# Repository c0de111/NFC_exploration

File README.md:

# NFC exploration

Sandbox repo to explore **ST25DV04KC (ISO15693 / NFC-V)** tap-to-trigger flows for power control and waking circuits such as inki.

## Goal
Build a small, reproducible test platform (ST25DV04KC + **Raspberry Pi Pico/RP2040** + antenna + simple enclosure) to validate:
- RF-field / `V_EH` wake behavior in the real case
- Phone → tag writes (EEPROM / Type 5)
- MCU reads request over I²C and clears/acks
- End-to-end timing assumptions for a future “tap-to-book” workflow

## Current validated behavior
- ST25DV04KC bring-up over I2C is stable on Pico (`GP20/GP21`), with ST25 power switched by `GP18`.
- End-to-end NFC-V write from phone to tag user memory is working.
- Firmware parses 16-byte `INKI` request payloads from the last user-memory slot (`0x01F0` on ST25DV04KC).
- Firmware command opcode handling is active:
  - `0x11` -> `LED1` slow blink
  - `0x12` -> `LED1` fast blink (same onboard LED)
  - `0x01` -> legacy alias mapped to `LED1` slow blink
- Incomplete/invalid `INKI` frames are ignored (to avoid partial-write races).
- Valid requests are cleared only after `RF field` goes `OFF` (reduces interference with phone-side readback).
- Power latch is asserted early by Pico on boot (`GP28`) and auto-released after `NFC_AUTO_POWER_OFF_MS` (default `10000` ms).
- Runtime logging is event-driven: startup diagnostics once, then RF field edges and request actions only.

## Tuning firmware (antenna / power characterization)
A dedicated firmware (`nfc_tune`, source: `firmware/src/tune_main.c`) for real-time RF energy-harvesting characterization. It samples the ST25DV `V_EH` output via Pico ADC and renders a live scrolling bar graph in the terminal showing harvested power delta above baseline.

### What it measures
- ADC voltage on `V_EH` pin (default ADC1 = `GP27`), averaged and EMA-smoothed
- Delta above a startup baseline capture (no-RF reference)
- RF field state derived from voltage thresholds (configurable ON/OFF hysteresis)
- ST25 EH control register state (`EH_EN`, `EH_ON`, `FIELD_ON`, `VCC_ON`) via I2C

### Build and flash
```bash
make firmware-tune                    # build nfc_tune
# then either:
make firmware-tune-flash              # flash via SWD
# or drag-and-drop firmware/build/nfc_tune.uf2 in BOOTSEL mode
```

### Tuning workflow
1. Connect Pico via USB (serial + power).
2. Open terminal: `sudo tio /dev/ttyACM0`
3. Wait for baseline capture (keep RF away for ~2 seconds at boot).
4. Tap phone to antenna — the live graph shows `V_EH` delta in mV, RF ON/OFF transitions, session peak, and EH register state.
5. Adjust antenna matching (C2/C3 on `NFC_harness_V0`) and re-tap to compare coupling.
6. `Ctrl+C` to stop.

### Key CMake tuning parameters
All defaults are in `firmware/CMakeLists.txt`:
- `NFC_TUNE_ADC_INPUT` – ADC channel (default `1` = `GP27`)
- `NFC_TUNE_FIELD_ON_MV` / `NFC_TUNE_FIELD_OFF_MV` – RF detection hysteresis thresholds (default `9` / `4` mV)
- `NFC_TUNE_GRAPH_WIDTH` / `NFC_TUNE_GRAPH_HEIGHT` – terminal graph dimensions (default `72x20`)
- `NFC_TUNE_GRAPH_MAX_MV` – vertical scale (default `3000` mV)
- `NFC_TUNE_SAMPLE_COUNT` / `NFC_TUNE_REPORT_INTERVAL_MS` – samples per report and update rate

## Current Wake/Latch Circuitry (PCB: `NFC_harness_V0`)
- `Q1` (`TSM260P02CX`, P-MOS) is the high-side power switch:
  - source -> `Vbatt`
  - drain -> Pico `VSYS`
- ST25 `GPO_(OPEN_DRAIN)` and the `Q1` gate share the same control net (wake/power-on net).
- Gate network shaping:
  - `R4=1M` pull-up to `Vbatt`
  - `C5=22n` to GND (pulse shaping / hold)
- Pico latch-hold path:
  - Pico `GPIO28` (`NFC_POWER_HOLD_PIN`) -> `R5=100k` -> `Q2` base
  - `R9=50k` pulls base to GND
  - `Q2` collector also sinks the same gate-control net
- On this PCB revision, Pico `GPIO19` is unconnected.
- LED wiring status on this PCB revision:
  - Both blink commands (`0x11` slow, `0x12` fast) use the firmware power-LED output (onboard Pico/Pico W path).
  - `NFC_STATUS_LED_PIN` (default `GP15`) is currently not routed to a dedicated onboard LED footprint here (external LED/wire may be needed).

## Command Flow (Phone -> ST25 -> Pico)
1. Board is fully off (`Vbatt` connected, no USB, Pico unpowered).
2. Phone tap powers ST25 RF side and writes the 16-byte `INKI` payload (including opcode byte) over NFC-V into ST25 EEPROM, while Pico can still be fully off.
3. ST25 asserts `GPO` low on configured wake event (`RF_WRITE`), pulling `Q1` gate low and powering Pico.
4. Pico boots and immediately asserts `GPIO28` high to latch power through `Q2`.
5. Data transfer from ST25 to Pico happens after boot over I2C (not on GPO):
   - Pico powers ST25 VCC via `GP18`
   - firmware reads request bytes from the last ST25 user-memory slot
6. Firmware validates the payload, applies opcode behavior, queues clear for RF-OFF, and later clears the slot.
7. Firmware releases the latch after timeout (`NFC_AUTO_POWER_OFF_MS`, default `10000` ms; re-armed on accepted commands).

Note:
- Runtime-loop request processing still runs while RF field is ON, with clear deferred to RF field OFF.
- Additionally, at boot firmware now checks for a stored valid request. If RF field is already OFF, it applies the command immediately and clears it at boot.
- If no valid `INKI` request is found after wake and RF is already OFF, firmware releases the power latch immediately.

## Repository layout
- `docs/context.md` – running notes, decisions, history, and solved problems
- `firmware/` – Pico SDK firmware scaffold (RP2040) for ST25 I²C exploration  
  - `src/` app entry (`main.c` harness, `tune_main.c` tuning) and bus adapter
  - `third_party/st25dv/` vendored ST25DV driver (git subtree)  
  - `scripts/` build/flash/reset helpers  
  - `cmake/` Pico SDK import helper  
- `pcb/NFC_harness_V0/` – KiCad project (schematic, layout, CAM profile)
- `pcb/tools/run_pcb2gcode.sh` – shared pcb2gcode runner
- `pcb/components/` + `pcb/project-libraries/` – KiCad symbols/footprints (includes ST25DV package lib submodule)
- `datasheet/` – ST25DV04KC datasheet + app notes
- `android/` – NFC‑V test apps (writer + hello) *(not needed for Pico-only workflow)*

## Typical workflow (from repo root)
1) **Build firmware**: `make firmware` (uses `PICO_SDK_PATH`, default `$HOME/pico/pico-sdk`).
2) **Flash**:  
   - Drag‑and‑drop: copy `firmware/build/nfc_harness.uf2` to Pico in BOOTSEL mode, or  
   - SWD: `make firmware-flash` (OpenOCD + CMSIS-DAP).
3) **Iterate**: edit `firmware/src/main.c` (and future helpers), rebuild, and re‑flash.
4) **CAM / milling** (optional): `pcb/tools/run_pcb2gcode.sh -b NFC_harness_V0` to regenerate toolpaths.

## Build & flash (Pico / RP2040)

### Build
```bash
# from repo root (recommended)
make firmware

# or inside firmware/
cd firmware
./scripts/build.sh   # expects $PICO_SDK_PATH (defaults to $HOME/pico/pico-sdk)
```
More detail (pin overrides, UF2 path, picotool toggles): see `firmware/README.md`.

Notes:
- Picotool is disabled by default to avoid downloads. The build script auto-fetches `uf2conv.py` (Microsoft UF2 tool) on first run and converts `nfc_harness.bin` → `nfc_harness.uf2`.
- Set `-DPICO_NO_PICOTOOL=OFF` in `cmake` if you prefer the picotool UF2/signing path.

Clean build artifacts:
```bash
make clean   # removes firmware/build only
```

Flash options:
- **USB drag‑and‑drop**: copy `firmware/build/nfc_harness.uf2` to the Pico mass‑storage device (BOOTSEL).
- **SWD (OpenOCD + CMSIS‑DAP probe)**:
  ```bash
  cd firmware
  ./scripts/flash.sh
  ```

### Root make targets (quick reference)
- `make firmware` – configure & build firmware into `firmware/build/`
- `make firmware-tune` – build dedicated antenna tuning firmware (`nfc_tune`)
- `make firmware-flash` – flash over SWD (OpenOCD + CMSIS‑DAP)
- `make firmware-tune-flash` – flash tuning firmware ELF over SWD
- `make clean` – remove `firmware/build/` only

## CAM workflow (pcb2gcode)
From repo root:
```bash
pcb/tools/run_pcb2gcode.sh -b NFC_harness_V0
```
The profile lives at `pcb/NFC_harness_V0/cam/pcb2gcode/profiles/default.millprojects` and uses repo-relative paths.

## Quick RF test (phone + Pico)
1. Connect a loop antenna to `J3` (`AC0`/`AC1`) on the PCB.
2. Build and flash firmware:
   - `make firmware`
   - copy `firmware/build/nfc_harness.uf2` to Pico in BOOTSEL mode (or use SWD).
3. Open serial logs:
   - `sudo tio /dev/ttyACM0`
4. On phone, open the NFC-V app (`inki`):
   - pick command button: `LED1 Slow` or `LED2 Fast`
5. Tap phone to antenna and hold briefly.

Expected runtime log pattern:
- `RF field: ON`
- `Request@0x01F0: ...`
- `INKI request: version=... opcode=... duration_min=...`
- `Command applied: opcode=... -> ...`
- `Queued clear after RF field OFF`
- `RF field: OFF`
- `Cleared request after RF OFF (...)`
- `Auto power-off: GP28 -> LOW`

Sample serial log (successful run):
```text
[INFO] RF field: OFF
[INFO] RF field: ON
[INFO] Request@0x01F0: 49 4E 4B 49 01 11 3C 00 ...
[OK] INKI request: version=1 opcode=0x11 duration_min=60 unix=... nonce=...
[OK] Command applied: opcode=0x11 -> LED1 slow blink
[INFO] Queued clear after RF field OFF
[INFO] RF field: OFF
[OK] Cleared request after RF OFF (16 bytes @ 0x01F0, attempts=1, 8ms)
[WARN] Auto power-off: GP28 -> LOW
```

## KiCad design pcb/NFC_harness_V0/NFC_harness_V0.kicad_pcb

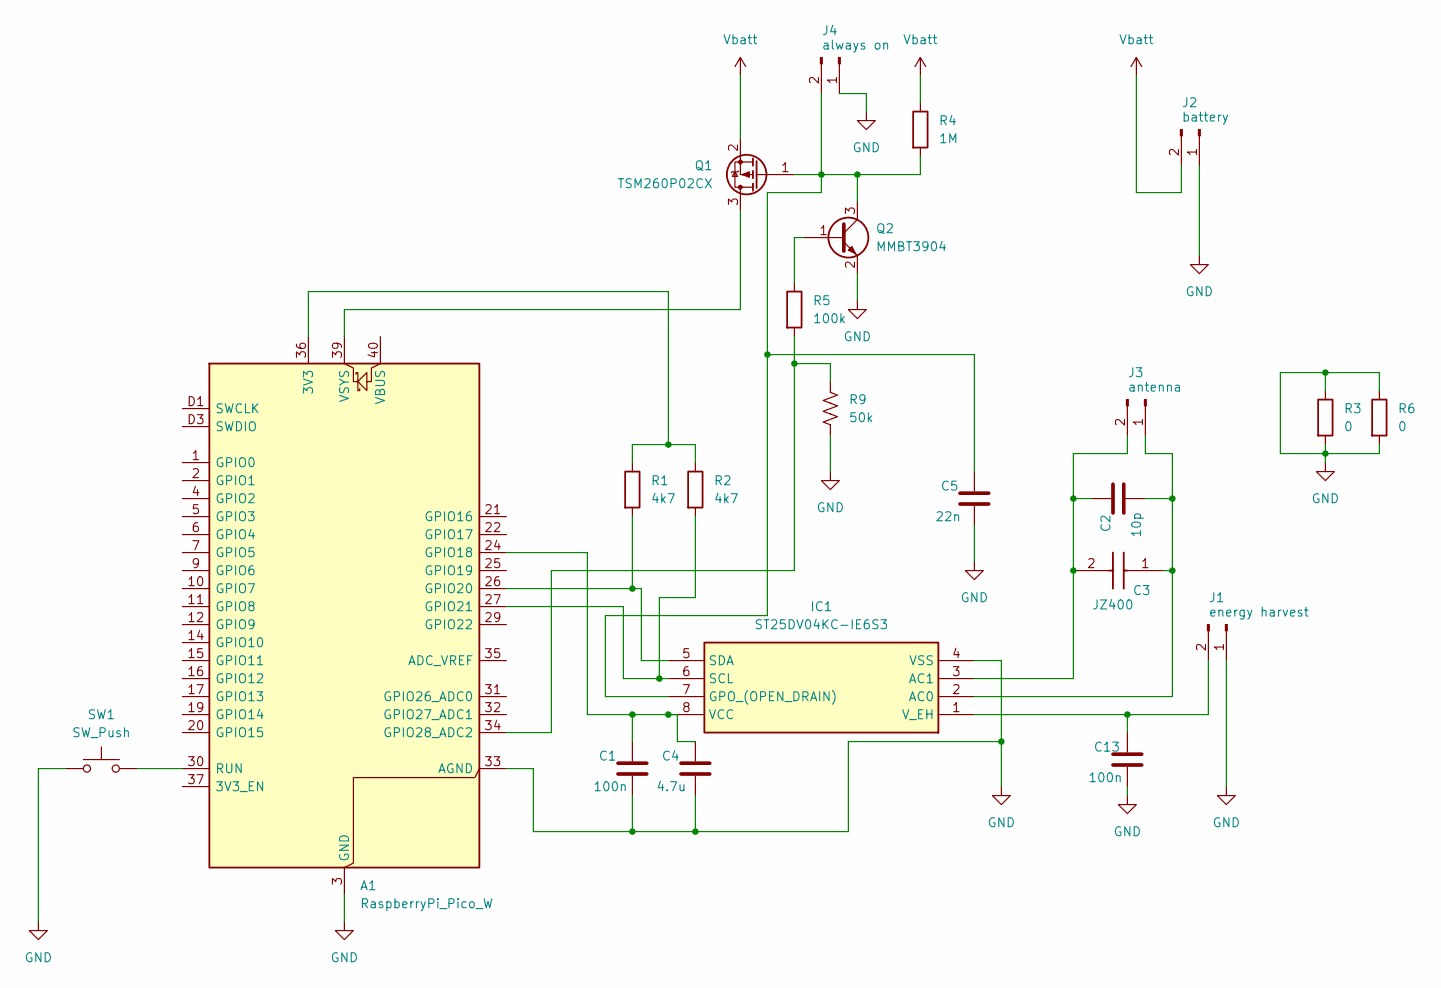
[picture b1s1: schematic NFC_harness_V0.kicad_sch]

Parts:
A1: RaspberryPi_Pico_W; RaspberryPi_Pico_W_SMD
C1, C13: 100n; C_0805_2012Metric
C2: 10p; C_0805_2012Metric
C3: JZ400; Mouser Part Number 768-JZ400
C4: 4.7u; C_1206_3216Metric
C5: 22n; C_0805_2012Metric
IC1: ST25DV04KC-IE6S3; SOIC127P600X175-8N; Mouser Part Number 511-ST25DV04KC-IE6S3
J1: energy harvest; PinHeader_1x02_P2.54mm_Vertical
J2: battery; PinHeader_1x02_P2.54mm_Vertical
J3: antenna; PinHeader_1x02_P2.54mm_Vertical
J4: always on; PinHeader_1x02_P2.54mm_Vertical
Q1: TSM260P02CX; SOT-23_Handsoldering
Q2: MMBT3904; SOT-23
R1, R2: 4k7; Fuse_1206_3216Metric_Pad1.42x1.75mm_HandSolder
R3, R6: 0; Fuse_1206_3216Metric_Pad1.42x1.75mm_HandSolder
R4: 1M; R_0805_2012Metric_Pad1.20x1.40mm_HandSolder
R5: 100k; Fuse_1206_3216Metric_Pad1.42x1.75mm_HandSolder
R9: 50k; Fuse_1206_3216Metric_Pad1.42x1.75mm_HandSolder
SW1: SW_Push; Taster 9313

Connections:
GND: A1.3 (GND), A1.8 (GND), A1.13 (GND), A1.18 (GND), A1.23 (GND), A1.28 (GND), A1.33 (AGND), A1.38 (GND), A1.D2 (GND), C1.2, C4.2, C5.2, C13.2, IC1.4 (VSS), J1.1, J2.1, J4.1, Q2.2 (E), R3.1, R3.2, R6.1, R6.2, R9.2, SW1.1
unnamed: A1.36 (3V3), R1.1, R2.1
unnamed: A1.24 (GPIO18), C1.1, C4.1, IC1.8 (VCC)
unnamed: A1.26 (GPIO20), IC1.5 (SDA), R1.2
unnamed: A1.27 (GPIO21), IC1.6 (SCL), R2.2
unnamed: A1.34 (GPIO28_ADC2), R5.2, R9.1
unnamed: A1.30 (RUN), SW1.2
unnamed: A1.39 (VSYS), Q1.3 (D)
unnamed: C2.2, C3.1, IC1.2 (AC0), J3.1
unnamed: C2.1, C3.2, IC1.3 (AC1), J3.2
unnamed: C5.1, IC1.7 (GPO_(OPEN_DRAIN)), J4.2, Q1.1 (G), Q2.3 (C), R4.2
unnamed: C13.1, IC1.1 (V_EH), J1.2
unnamed: Q2.1 (B), R5.1
Vbatt: J2.2, Q1.2 (S), R4.1

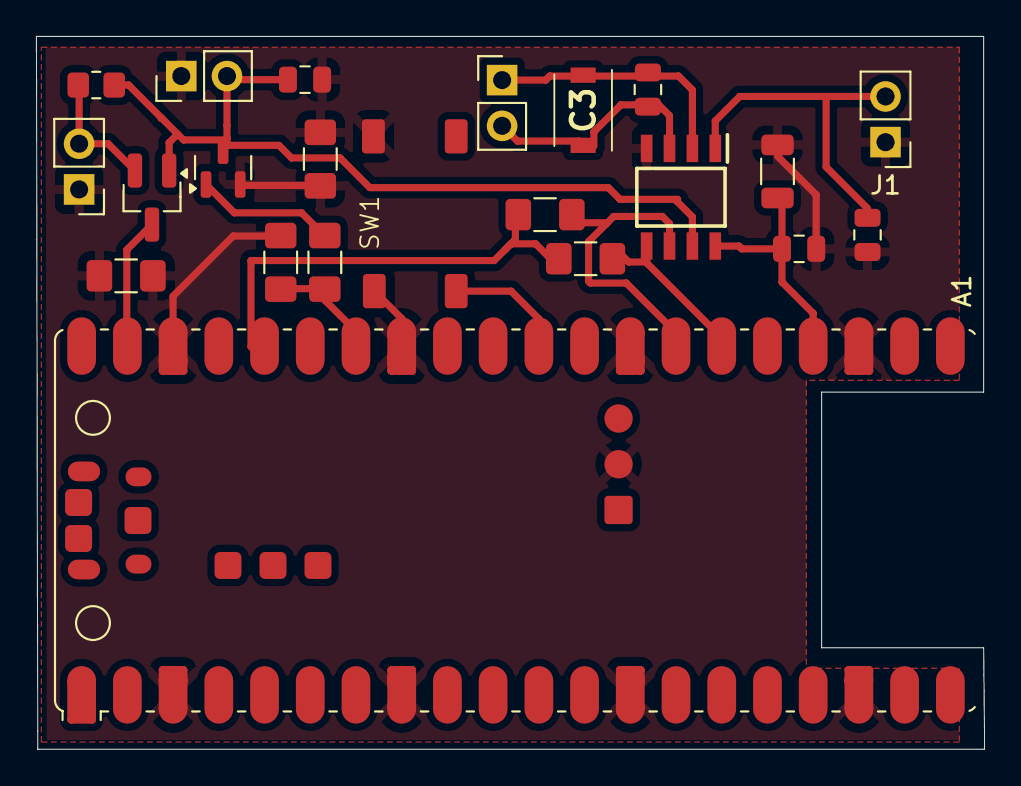
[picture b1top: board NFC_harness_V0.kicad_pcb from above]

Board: 2 copper layers, 52.7 x 39.6 mm, 22 parts (0 on the bottom side), 14 nets.

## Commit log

2026-01-25 initial commit - use PlaygroundSentinelV2 as starting point
2026-01-28 initial commit - with tiny, will be changed to pico
2026-01-28 changed to pico
2026-01-28 Squashed 'firmware/c/third_party/' content from commit 7088a8a
    git-subtree-dir: firmware/c/third_party
    git-subtree-split: 7088a8ad29b3ccc1c34ad6a055c4ac96ad8fde26
2026-01-28 Wire stm32-st25dv into Pico harness
2026-01-28 Document Pico SDK vs ST25DV driver integration
2026-01-28 Fix ST25DV API usage (use St25Dv_Drv entrypoints)
2026-01-28 Clarify ST driver entrypoints (St25Dv_Drv)
2026-01-28 Read/clear request at last-block start (block-size safe)
2026-01-28 added i2c to main.c
2026-01-28 pcb symbols st25
2026-01-31 reorg
2026-02-05 pcb work
2026-02-05 cam job output
2026-02-05 pcb update
2026-02-10 firmware: stabilize ST25DV bring-up and startup diagnostics
2026-02-10 firmware: harden RF request handling and defer clear after field-off
2026-02-10 docs: update README with validated RF flow and sample log
2026-02-10 firmware: clarify ST25 dynamic diagnostics and log GPO IT_TIME
2026-02-13 chore(gitignore): ignore KiCad local files and pcb2gcode outputs
2026-02-13 pcb: update NFC harness and add Taster 9313 footprint
2026-02-13 firmware: make I2C operation timeout configurable via CMake
2026-02-13 pcb edits
2026-02-15 Default pico_w LED, correct i2c default
2026-02-15 GPO implemented
2026-02-15 auto switch off and op code NFC
2026-02-15 Implement the NFC wake-to-command architecture end-to-end with robust boot/runtime request handling and visible single-LED command feedback, and document the updated flow.
2026-02-15 details about Android
2026-02-16 Harden the wake-to-command path by limiting ST25 GPO wake to RF_WRITE and immediately releasing the power latch when no valid INKI request is detected after wake.
2026-02-16 Add a default Android build entrypoint that enforces the local SDK path with explicit override support
2026-02-16 Implement the Android tap-flow UX overhaul with unified result overlays, inki branding/icon integration, and direct build-to-sync workflow automation.
2026-02-16 Exclude Android Kotlin session metadata from version control and remove transient IDE session artifacts.
2026-02-16 Refactor Android tap UI to use scalable active-state command buttons with toggle-group mapping and update docs/context accordingly.
2026-03-15 Document the EH tuning mode for real-time antenna and power-harvesting characterization in the README.
2026-03-15 Establish a Pico-first tuning firmware path by adding nfc_tune with robust ST25DV energy-harvesting telemetry and aligning build scripts, Make targets, and docs around the new workflow. With Acii art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
2026-03-15 context
2026-03-15 Wire NFC_ENABLE_EH_TEST_MODE through CMake cache and clarify README rebuild instructions.
2026-03-15 Rewrite README tuning section to document the dedicated nfc_tune ADC-based firmware and its workflow.
2026-04-05 initial release
2026-04-25 Clarify README description for sandbox repo
    Updated the README to clarify the purpose of the sandbox repo.
